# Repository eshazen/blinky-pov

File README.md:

# Blinky POV

This is a copy of designs from the EDF SVN for Blinky POV (persistence
of vision) toys for soldering training and outreach.

**AVR4** - Version 4 of thru-hole design using an ATTiny44A MCU.
This includes firmware and HTML blinky programming code

**BlinkyColorPOV** - Version using RGB LEDs.  Some issues with
soldering the 4-pin LEDs.  Probably overly-complex for a new project.

See https://github.com/eshazen/blinky-avr-smt for a newer version
based loosely on AVR4.

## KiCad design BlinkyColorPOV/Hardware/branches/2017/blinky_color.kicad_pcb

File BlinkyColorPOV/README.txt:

This repository contains the documentation and firmware for the "Blinky Color POV"
gadget, which displays text in color when waved back and forth in the air.

Downloading is accomplished using a variation of the "Blinky POV" optical download
technique by Wayne&Layne.  See: http://www.wayneandlayne.com/projects/blinky/

Hardware  	       KiCAD PCB layout and gerber files
		       Hardware/gerber/blinky_color2.zip is latest fab package

Firmware/ColorText     Firmware for final version
		       Edit makefile as required for download cable, then
		       'make fuse' and 'make flash'

Programming	       Javascript download tool
		       use 'colortext.html', with on-screen documentation

myFont2c	       Contains 'fontExtract' tool which converts an X11 bitmap
		       font to javascript data

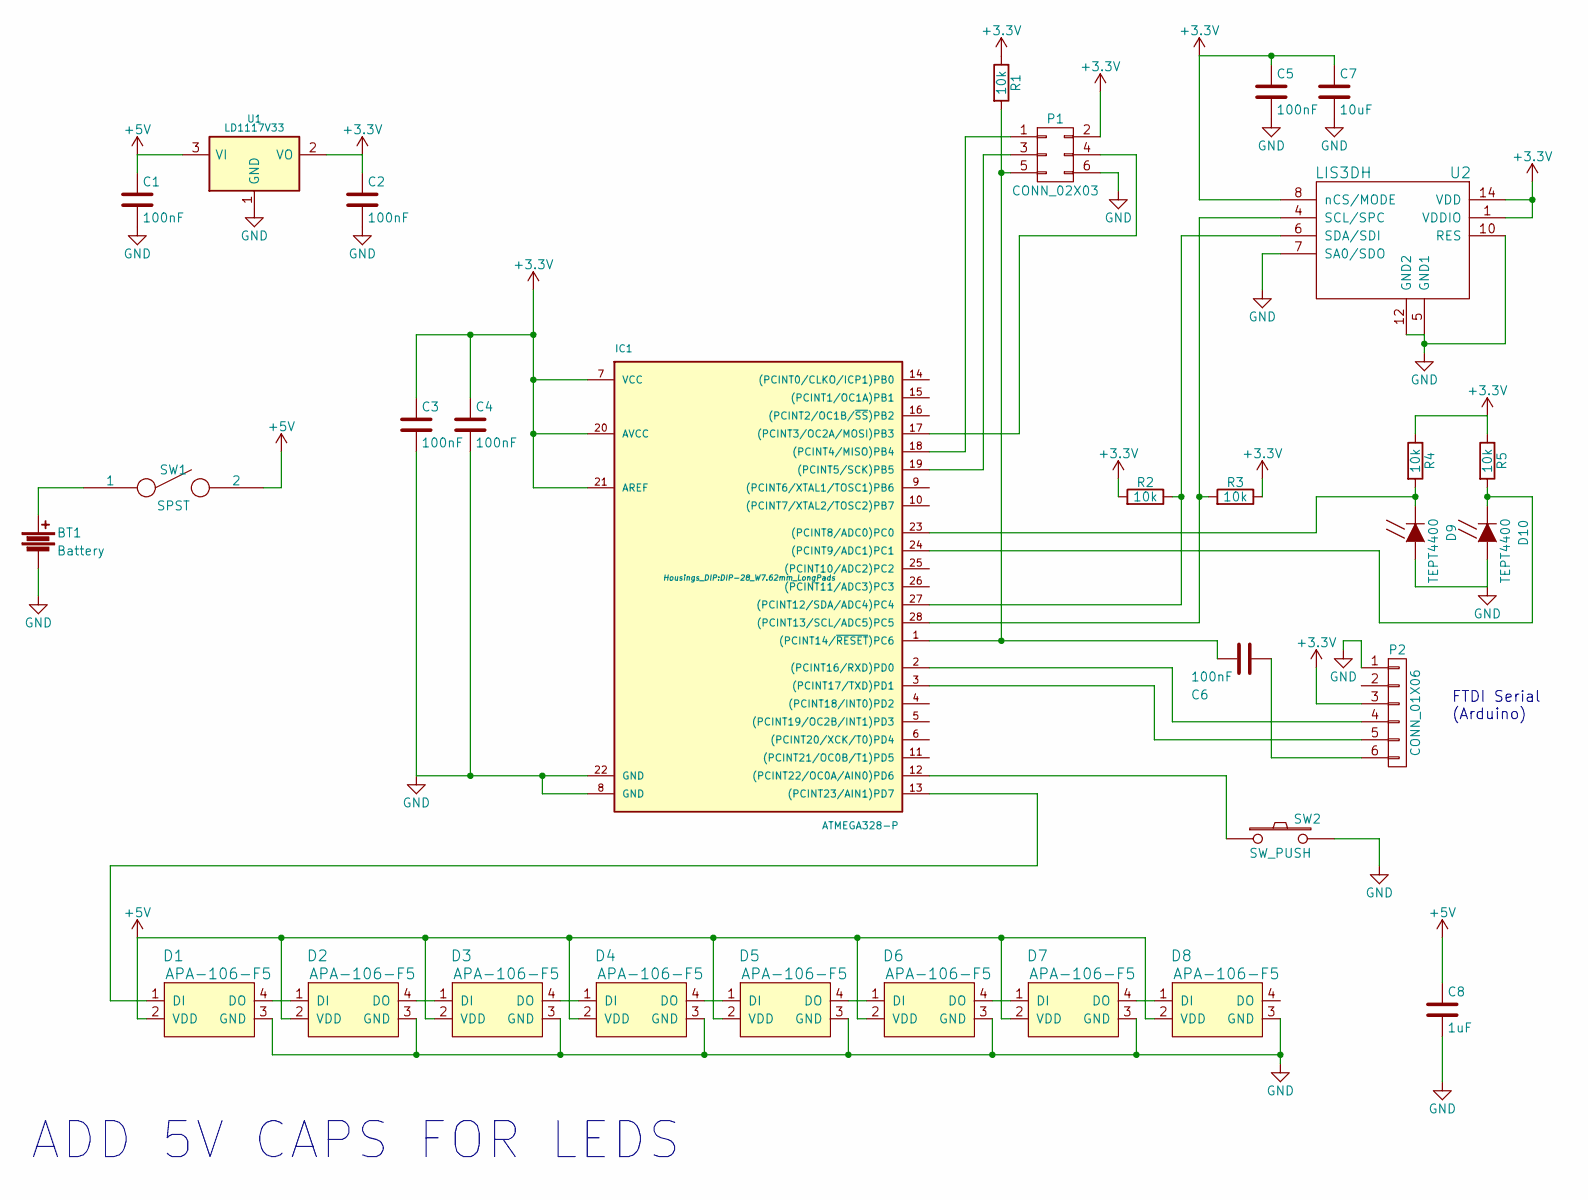
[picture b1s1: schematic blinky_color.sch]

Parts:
BT1: Battery; AAA_batterypack
C1, C5: 100nF; C_Rect_L7.0mm_W2.0mm_P5.00mm
C2, C3, C4, C6: 100nF; C_Rect_L7_W2_P5
C7: 10uF; C_Rect_L7.0mm_W2.0mm_P5.00mm
C8: 1uF; C_Rect_L7_W2_P5
D1, D2, D3, D4, D5, D6, D7, D8: APA-106-F5; bornier4
D9, D10: TEPT4400; Diode_P600_Vertical_AnodeUp
IC1: ATMEGA328-P; DIP-28_W7.62mm_LongPads
P1: CONN_02X03; Pin_Header_Straight_2x03
P2: CONN_01X06; Pin_Header_Straight_1x06
R1, R2, R3, R4, R5: 10k; Resistor_Horizontal_RM10mm
SW1: SPST; SW_Micro_SPST
SW2: SW_PUSH; SW_PUSH-12mm
U1: LD1117V33; TO-220_Neutral123_Vertical
U2: LIS3DH; lga16

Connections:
+3V3: C2.1, C3.1, C4.1, C5.1, C7.1, IC1.7 (VCC), IC1.20 (AVCC), IC1.21 (AREF), P1.2, P2.3, R1.1, R2.2, R3.1, R4.1, R5.1, U1.2 (VO), U2.1 (VDDIO), U2.8 (nCS/MODE), U2.14 (VDD)
+5V: C1.1, C8.1, D1.2 (VDD), D2.2 (VDD), D3.2 (VDD), D4.2 (VDD), D5.2 (VDD), D6.2 (VDD), D7.2 (VDD), D8.2 (VDD), SW1.2, U1.3 (VI)
GND: BT1.2, C1.2, C2.2, C3.2, C4.2, C5.2, C7.2, C8.2, D1.3 (GND), D2.3 (GND), D3.3 (GND), D4.3 (GND), D5.3 (GND), D6.3 (GND), D7.3 (GND), D8.3 (GND), D9.2 (A), D10.2 (A), IC1.8 (GND), IC1.22 (GND), P1.6, P2.1, SW2.2, U1.1 (GND), U2.5 (GND1), U2.7 (SA0/SDO), U2.10 (RES), U2.12 (GND2)
unnamed: BT1.1, SW1.1
unnamed: C6.1, P2.6
unnamed: C6.2, IC1.1 ((PCINT14/~RESET~)PC6), P1.5, R1.2
unnamed: D1.1 (DI), IC1.13 ((PCINT23/AIN1)PD7)
unnamed: D1.4 (DO), D2.1 (DI)
unnamed: D2.4 (DO), D3.1 (DI)
unnamed: D3.4 (DO), D4.1 (DI)
unnamed: D4.4 (DO), D5.1 (DI)
unnamed: D5.4 (DO), D6.1 (DI)
unnamed: D6.4 (DO), D7.1 (DI)
unnamed: D7.4 (DO), D8.1 (DI)
unnamed: D9.1 (K), IC1.23 ((PCINT8/ADC0)PC0), R4.2
unnamed: D10.1 (K), IC1.24 ((PCINT9/ADC1)PC1), R5.2
unnamed: IC1.2 ((PCINT16/RXD)PD0), P2.4
unnamed: IC1.3 ((PCINT17/TXD)PD1), P2.5
unnamed: IC1.12 ((PCINT22/OC0A/AIN0)PD6), SW2.1
unnamed: IC1.17 ((PCINT3/OC2A/MOSI)PB3), P1.4
unnamed: IC1.18 ((PCINT4/MISO)PB4), P1.1
unnamed: IC1.19 ((PCINT5/SCK)PB5), P1.3
unnamed: IC1.27 ((PCINT12/SDA/ADC4)PC4), R2.1, U2.6 (SDA/SDI)
unnamed: IC1.28 ((PCINT13/SCL/ADC5)PC5), R3.2, U2.4 (SCL/SPC)

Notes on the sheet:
FTDI Serial (Arduino)
ADD 5V CAPS FOR LEDS

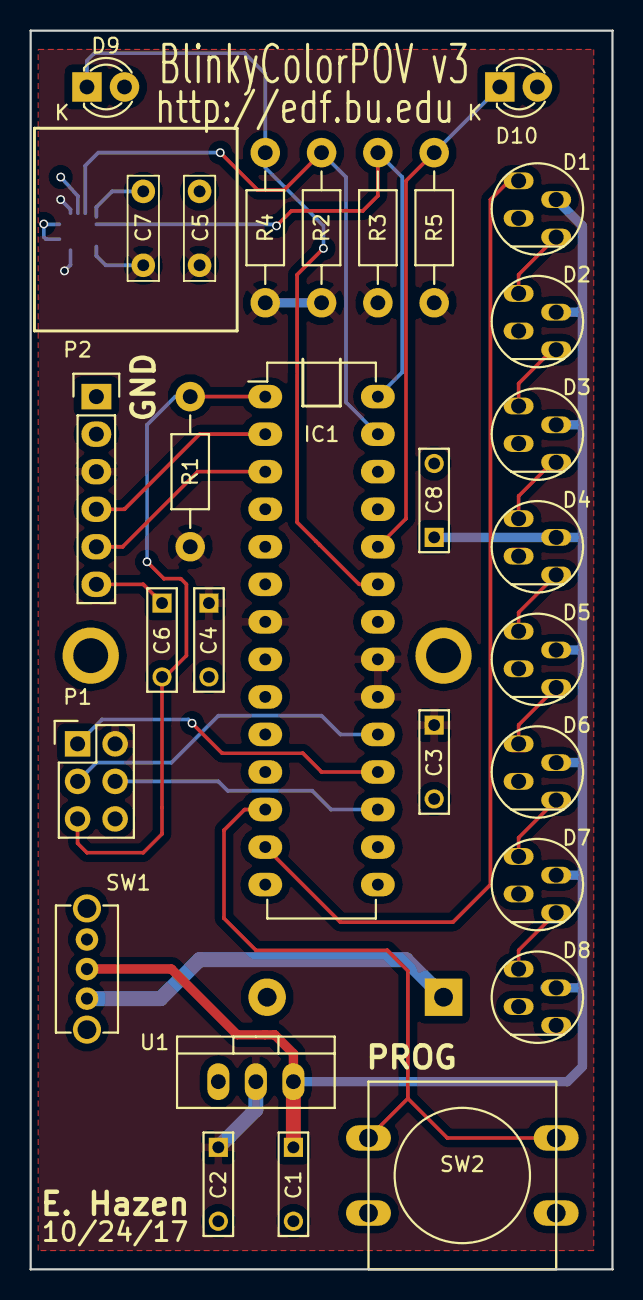
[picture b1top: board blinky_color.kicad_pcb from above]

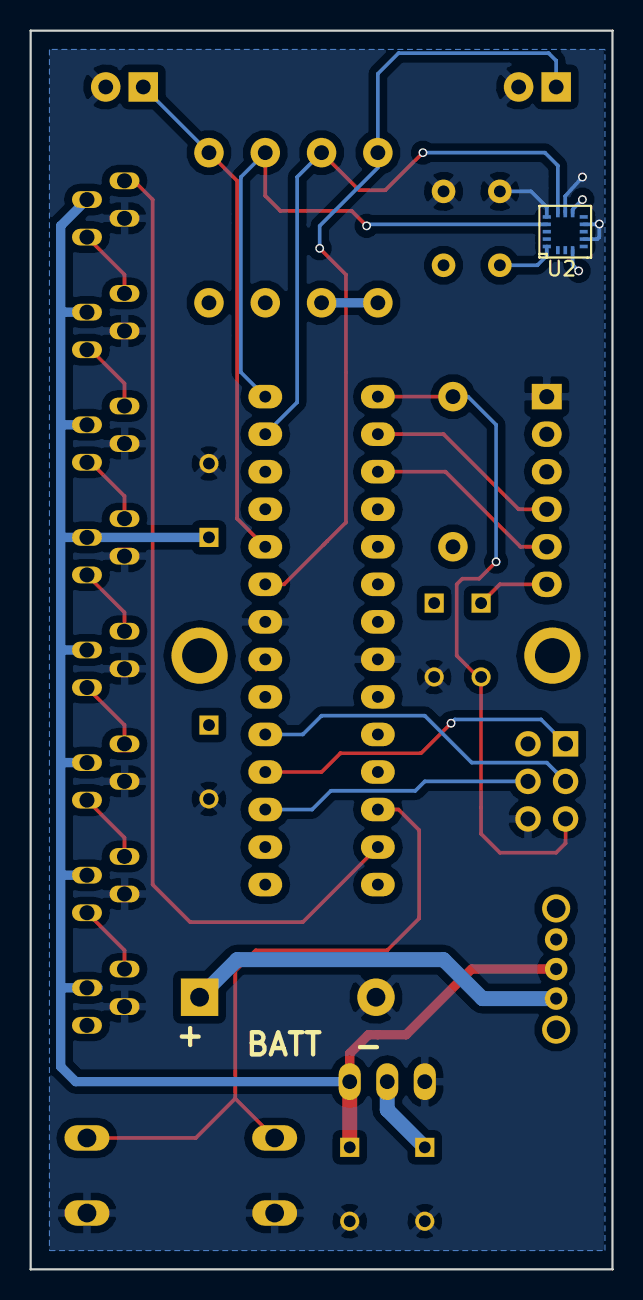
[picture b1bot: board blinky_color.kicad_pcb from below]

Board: 2 copper layers, 39.4 x 83.8 mm, 31 parts (2 on the bottom side), 24 nets.

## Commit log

2023-09-16 initial copy from SVN (no history)
